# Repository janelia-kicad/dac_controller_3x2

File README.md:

- [Repository Information](#org372c64f)
  - [Description](#orgae9022b)
- [Images](#org44ae73a)
- [Schematic](#orga211832)
- [Gerbers](#org3493c07)
- [Bill of Materials](#org3fd8118)
  - [PCB Parts](#org3846433)
  - [Supplemental Parts](#org2a14c79)
  - [Vendor Parts Lists](#org9ceb174)
- [Supplemental Documentation](#org9992682)
  - [Assembly Instructions](#org5a3e1bd)

# Repository Information

-   **Name:** dac\_controller\_3x2
-   **Version:** 1.0
-   **License:** Open-Source Hardware
-   **URL:** <https://github.com/janelia-kicad/dac_controller_5x3>
-   **Author:** Peter Polidoro
-   **Email:** peter@polidoro.io

## Description

This board controls four 16-bit unipolar/bipolar voltage DAC output channels.

# Images

# Schematic

[./schematic/dac\_controller\_3x2.pdf](./schematic/dac_controller_3x2.pdf)

# Gerbers

Send gerbers zip file to your favorite PCB manufacturer for fabrication.

[./gerbers/dac\_controller\_3x2\_v1.0.zip](./gerbers/dac_controller_3x2_v1.0.zip)

# Bill of Materials

## PCB Parts

| Item | Reference(s) | Quantity | PartNumber             | Vendor  | Description                               |
|---- |------------ |-------- |---------------------- |------- |----------------------------------------- |
| 1    | C1 C3 C5     | 3        | 445-4536-1-ND          | digikey | CAP CER 10UF 50V 10% X7S 1210             |
| 2    | C2 C4 C6     | 3        | 399-13229-1-ND         | digikey | CAP CER 0.1UF 50V 10% X7R 1210            |
| 3    | D1           | 1        | AD5754RBREZ-REEL7CT-ND | digikey | IC DAC 16BIT DSP/SRL 24TSSOP              |
| 4    | MDB1         | 2        | S1011E-16-ND           | digikey | 16 Position Header Through Hole Male Pins |
| 5    | P1 P2        | 2        | ACX1655-ND             | digikey | CONN BNC JACK R/A 75 OHM PCB              |
| 6    | REG1         | 1        | 945-1579-5-ND          | digikey | DC DC CONVERTER +/-12V 1W                 |

## Supplemental Parts

| Item | Quantity | PartNumber  | Vendor  | Description                     |
|---- |-------- |----------- |------- |------------------------------- |
| 1    | 4        | 290-1026-ND | digikey | CBL ASSY BNC PLUG-PLUG RG59 6FT |

## Vendor Parts Lists

[./bom/digikey\_parts.csv](./bom/digikey_parts.csv)

[./bom/supplemental\_digikey\_parts.csv](./bom/supplemental_digikey_parts.csv)

# Supplemental Documentation

## Assembly Instructions

-   Solder surface mount and through hole components onto the pcb.

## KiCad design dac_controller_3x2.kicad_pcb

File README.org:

# Created 2018-09-17 Mon 12:38
#+OPTIONS: title:nil author:nil email:nil toc:t |:t ^:nil
* Repository Information

- Name :: dac_controller_3x2
- Version :: 1.0
- License :: Open-Source Hardware
- URL :: https://github.com/janelia-kicad/dac_controller_5x3
- Author :: Peter Polidoro
- Email :: peter@polidoro.io

** Description

This board controls four 16-bit unipolar/bipolar voltage DAC output channels.

* Images

* Schematic

[[file:./schematic/dac_controller_3x2.pdf][./schematic/dac_controller_3x2.pdf]]

[[file:./schematic/images/schematic00.png]]

[[file:./schematic/images/schematic01.png]]

* Gerbers

Send gerbers zip file to your favorite PCB manufacturer for fabrication.

[[file:./gerbers/dac_controller_3x2_v1.0.zip][./gerbers/dac_controller_3x2_v1.0.zip]]

[[file:./gerbers/images/gerbers00.png]]

[[file:./gerbers/images/gerbers01.png]]

* Bill of Materials

** PCB Parts

| Item | Reference(s) | Quantity | PartNumber             | Vendor  | Description                               |
|------+--------------+----------+------------------------+---------+-------------------------------------------|
|    1 | C1 C3 C5     |        3 | 445-4536-1-ND          | digikey | CAP CER 10UF 50V 10% X7S 1210             |
|    2 | C2 C4 C6     |        3 | 399-13229-1-ND         | digikey | CAP CER 0.1UF 50V 10% X7R 1210            |
|    3 | D1           |        1 | AD5754RBREZ-REEL7CT-ND | digikey | IC DAC 16BIT DSP/SRL 24TSSOP              |
|    4 | MDB1         |        2 | S1011E-16-ND           | digikey | 16 Position Header Through Hole Male Pins |
|    5 | P1 P2        |        2 | ACX1655-ND             | digikey | CONN BNC JACK R/A 75 OHM PCB              |
|    6 | REG1         |        1 | 945-1579-5-ND          | digikey | DC DC CONVERTER +/-12V 1W                 |

** Supplemental Parts

| Item | Quantity | PartNumber  | Vendor  | Description                     |
|------+----------+-------------+---------+---------------------------------|
|    1 |        4 | 290-1026-ND | digikey | CBL ASSY BNC PLUG-PLUG RG59 6FT |

** Vendor Parts Lists

[[file:./bom/digikey_parts.csv][./bom/digikey_parts.csv]]

[[file:./bom/supplemental_digikey_parts.csv][./bom/supplemental_digikey_parts.csv]]

* Supplemental Documentation

** Assembly Instructions

- Solder surface mount and through hole components onto the pcb.

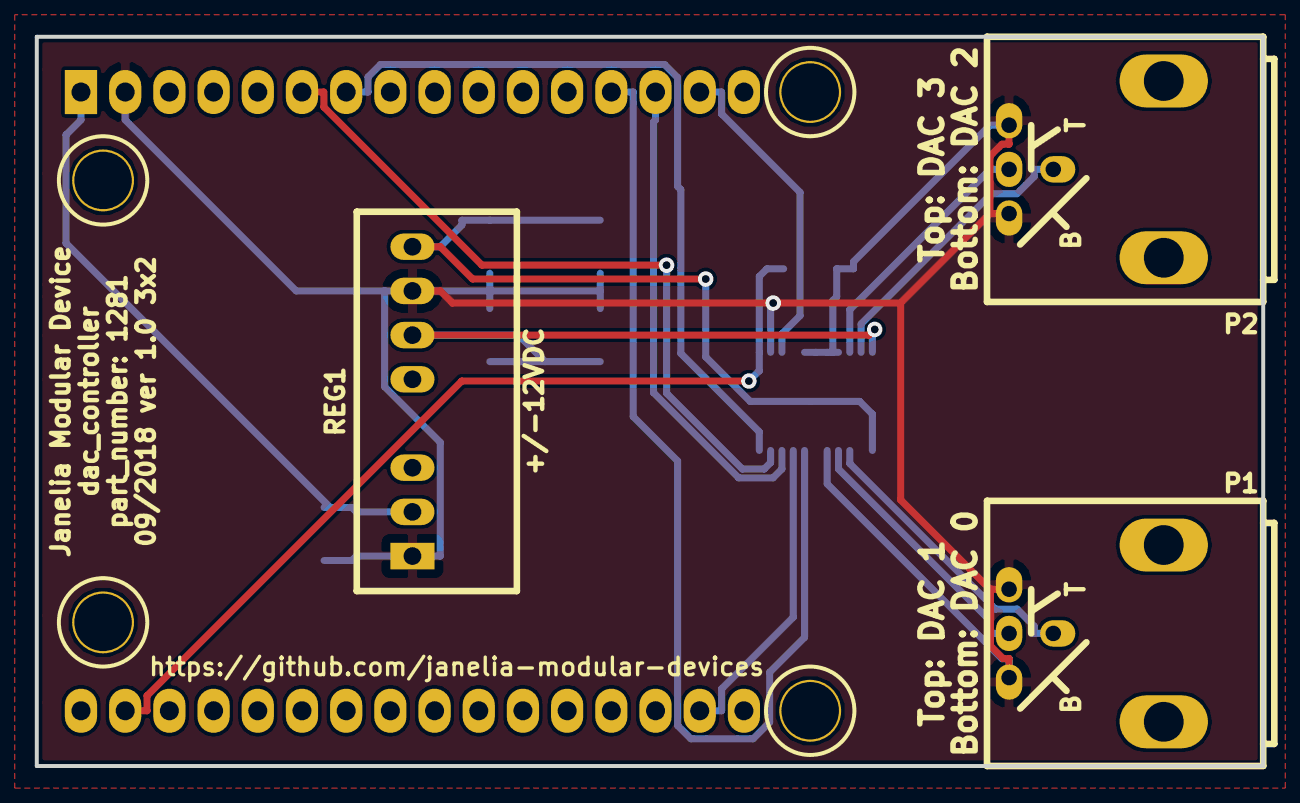
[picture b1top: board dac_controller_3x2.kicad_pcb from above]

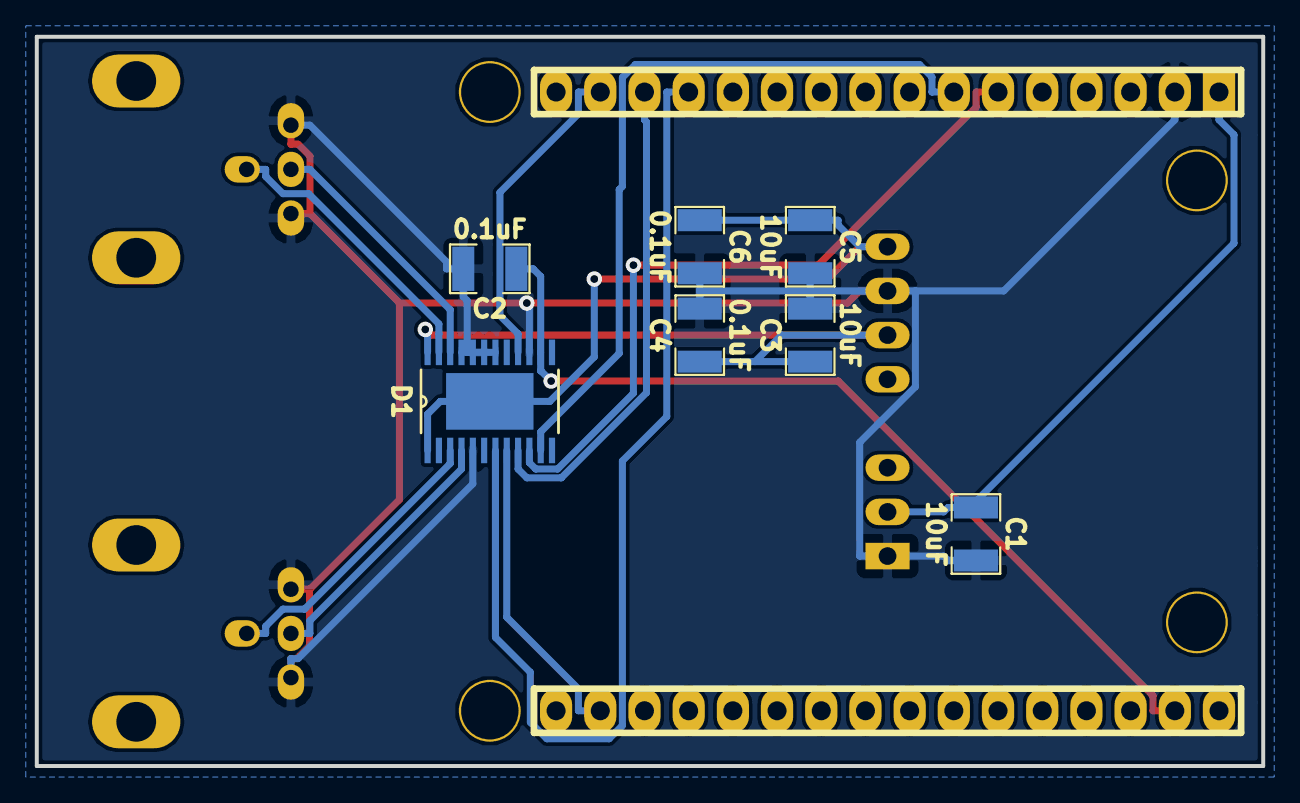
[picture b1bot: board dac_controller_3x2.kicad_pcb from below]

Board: 2 copper layers, 70.5 x 41.9 mm, 11 parts (7 on the bottom side), 15 nets.

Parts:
C1, C3, C5: 10uF; SM1210
C2, C4, C6: 0.1uF; SM1210
D1: AD5754R; TSSOP_EP_24
MDB1: MODULAR_DEVICE_BASE_3X2_MALE
P1, P2: BNC_DOUBLE_RA; BNC_DOUBLE
REG1: CONV_DC_DC_-12V_12V_1W; DC_DC_CONV_RSO

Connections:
/CLR: D1.11, MDB1.4
/CS: D1.7, MDB1.10
/LDAC: D1.10, MDB1.3
/MISO: D1.16, MDB1.12
/MOSI: D1.9, MDB1.11
/SCK: D1.8, MDB1.13
/dac_3x2/DAC_0: D1.3, P1.1
/dac_3x2/DAC_1: D1.4, P1.3
/dac_3x2/DAC_2: D1.23, P2.1
/dac_3x2/DAC_3: D1.22, P2.3
GND: C1.2, C2.2, C3.2, C4.2, C5.2, C6.2, D1.5, D1.15, D1.18, D1.19, D1.20, D1.21, MDB1.GND, P1.2, P1.4, P2.2, P2.4, REG1.1, REG1.7
VDD: C1.1, MDB1.VDD, REG1.2
VDDA: C3.1, C4.1, D1.24, REG1.6
VEE: C2.1, D1.14, MDB1.VEE
VSSA: C5.1, C6.1, D1.1, D1.25, REG1.8

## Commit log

2018-09-14 Initial commit.
2018-09-14 Initial layout.
2018-09-17 Finished v1.0.
2018-09-17 Updated bom and documentation.
2018-09-18 CS -> SS.
2018-09-18 SS -> CS.
2018-10-23 Updated submodules.
2018-11-02 Added README.md.
2021-09-16 Update email address
2021-09-21 Remove ignored files
2022-02-22 Add guix files
2022-02-23 Add guix documentation

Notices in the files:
parts and their libraries:
Copyright 2016 Accelerated Designs. All rights reserved.
